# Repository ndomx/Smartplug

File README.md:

# Smartplug
WiFi controller for home automation

## Description
A smartplug is a device with which you can control the conection of an appliance remotely. As of version 2, I'm using an ESP8266 micro-controller, and controlling it using MQTT.

The schematics are publicly available in this repository, and the fabrication files are available in the releases page. All the required codes are also publicly available here, though you'll have to setup your Arduino IDE to program the MCU. Refer to the [libraries guide](./LIBRARIES_GUIDE.md) to learn how to do it.

## Functionality
### Basics
The basic operation of the smartplug is fairly simple. It's a commutator circuit just like those lights, found commonly in stairs, that can be controlled by two switches. The circuit goes as follows:

Current can flow through the load (a light bulb) when bith switches are in the same state. The smartplug works the same way, but instead of having two switches, it has two relays that are controlled by the MCU.

The MCU controls both signals, **RELAY_A** and **RELAY_B** that toggle each switch. One control signal is controlled remotely (via MQTT) while the other is controlled by an external switch.

The smartplug has two modes of operation:
1. Take absolute control of the load remotely, i.e. connect/disconnect the load remotely regardless of the external switch input
2. Use the smartplug as a traditional commutator circuit, i.e. the load will toggle every time each control signal is toggled, wether its via MQTT or physical input

> I noticed only one relay is necessary to achieve the same behaviour. So V3 will drop one relay and handle all the logic by software.

The mode of operation is controlled by the header J4.

### Power
The PCB traces were calculated for 5A max. In countries with 220V/50Hz supply, this can power 1kW loads. In countries with 110V/60Hz, the max output power is limited to 0.5kW.

On the other hand, all the electronics can be powered by the AC/DC module **X1**, or by external 5V connected to the USB connector, as shown in the image below.

Connect the jumper **J5** to enable power input from the AC/DC module, or leave disconnected and power via USB cable.
> Powering the device via USB cable is meant for uploading the firmware to the MCU. For other purposes, the use of the AC/DC module is recommended

### Current sensing
The smartplug is equipped with an ACS712 current sensor. The current is measured by the MCU ADC and uploaded to the server.

Additionally, if and overcurrent is detected, the OC flag will be activated (~OC as it is active low) and the output will be disabled.

The SN74LV (**U1**) is a quad NAND gate that implements the logic circuit that ensures the load remains unconnected while the OC flag is active.

When ~OC goes low, the outputs **RELAY_A** and **RELAY_B** will go HIGH/LOW repectively, thus, shutting down the load.

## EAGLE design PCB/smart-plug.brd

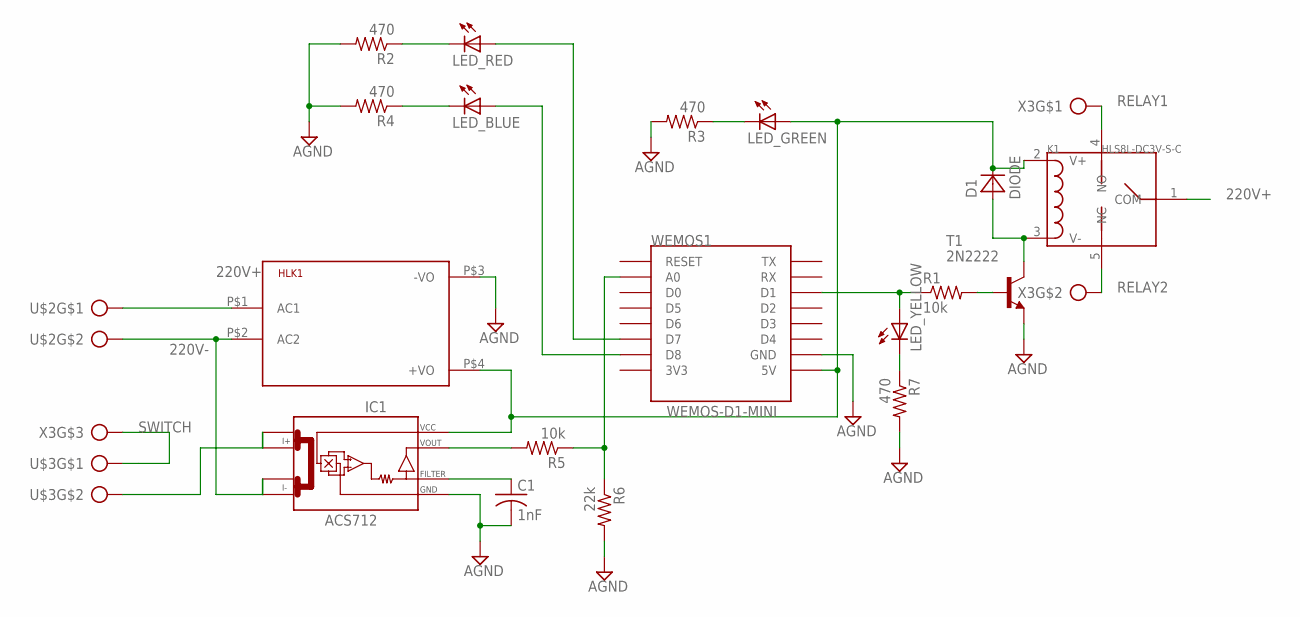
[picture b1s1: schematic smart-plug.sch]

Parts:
C1: 1nF; C1206
D1: DIODE; DO41-10
HLK1: HLK-SUPPLY; HLK-PM01
IC1: ACS712; SO08
K1: HLS8L-DC3V-S-C; REY5-19.0X15.0X15.0MM
LED_BLUE: LEDCHIP-LED0805; CHIP-LED0805
LED_GREEN: LEDCHIP-LED0805; CHIP-LED0805
LED_RED: LEDCHIP-LED0805; CHIP-LED0805
LED_YELLOW: LEDCHIP-LED0805; CHIP-LED0805
R1, R5: 10k; R1206
R2, R3, R4, R7: 470; R1206
R6: 22k; R1206
T1: 2N2222; TO92-EBC-OVAL
U$2, U$3: OUT-2PINS; AK300/2
WEMOS1: WEMOS-D1-MINI
X3: OUT-3PINS; AK300/3

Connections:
220V+: HLK1.P$1 (AC1), K1.1 (COM), U$2.1
220V-: HLK1.P$2 (AC2), IC1.4 (I-_1), U$2.2
AGND: C1.2, HLK1.P$3 (-VO), IC1.5 (GND), R2.2, R3.2, R4.2, R6.2, R7.2, T1.E, WEMOS1.GND
LED_BLUE: LED_BLUE.A, WEMOS1.D8
LED_GREEN: LED_GREEN.C, R3.1
LED_GREEN1: LED_YELLOW.C, R7.1
LED_RED: LED_RED.A, WEMOS1.D7
unnamed: IC1.2 (I+_1), U$3.2
unnamed: LED_YELLOW.A, R1.1, WEMOS1.D1
unnamed: R1.2, T1.B
unnamed: D1.C, HLK1.P$4 (+VO), IC1.8 (VCC), K1.2 (V+), LED_GREEN.A, WEMOS1.5V
unnamed: C1.1, IC1.6 (FILTER)
unnamed: D1.A, K1.3 (V-), T1.C
unnamed: IC1.7 (VOUT), R5.2
unnamed: R5.1, R6.1, WEMOS1.A0
unnamed: LED_RED.C, R2.1
unnamed: LED_BLUE.C, R4.1
RELAY1: K1.4 (NO), X3.1
RELAY2: K1.5 (NC), X3.2
SWITCH: U$3.1, X3.3

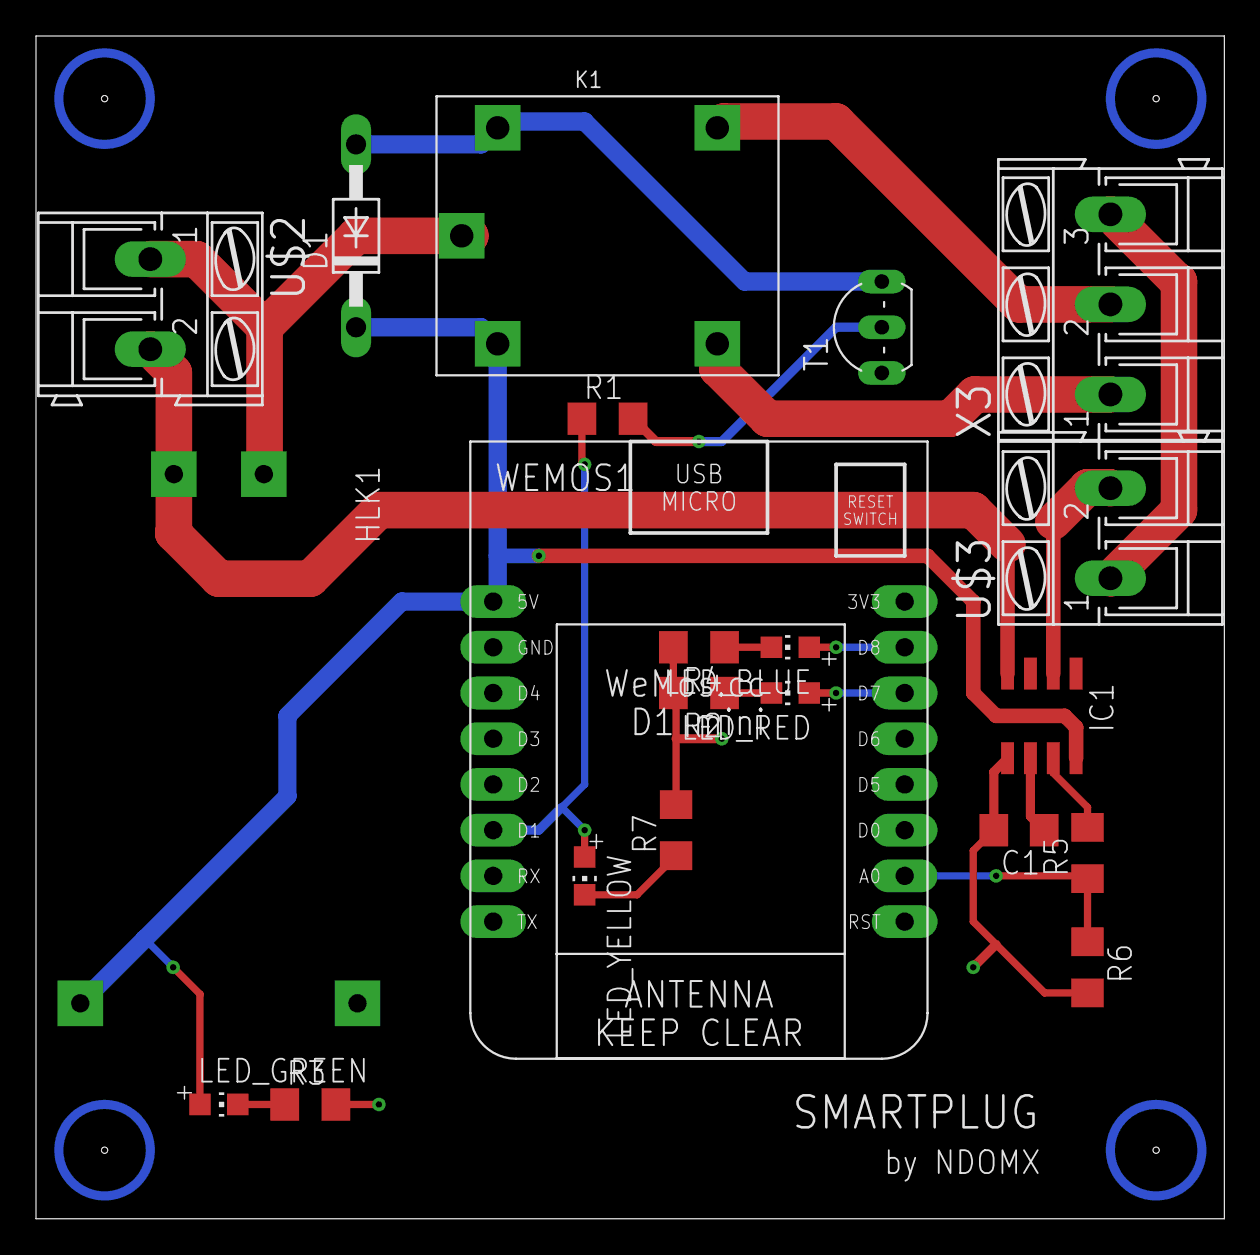
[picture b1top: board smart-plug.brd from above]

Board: 2 copper layers, 66.0 x 65.7 mm, 21 parts (0 on the bottom side), 20 nets.

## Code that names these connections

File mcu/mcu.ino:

#include <ESP8266WiFi.h>
#include <PubSubClient.h>

#include "private-data.h"

#define RELAY_PIN D1
#define LED_RED D6
#define LED_GREEN D7
#define LED_BLUE D8

String clientId = "ESP8266-light1"; // Be sure to change it for each device

WiFiClient espClient;
PubSubClient client(espClient);

bool blue_state = LOW;

void setup_wifi()
{
    delay(10);
    
    Serial.println();
    Serial.print("Connecting to ");
    Serial.println(ssid);

    WiFi.begin(ssid, password);

    while (WiFi.status() != WL_CONNECTED)
    {
        delay(500);
        Serial.print(".");

        digitalWrite(LED_BLUE, blue_state);
        blue_state ^= HIGH;
    }

    blue_state = LOW;
    digitalWrite(LED_BLUE, LOW);

    randomSeed(micros());

    Serial.println("");
    Serial.println("WiFi connected");
    Serial.println("IP address: ");
    Serial.println(WiFi.localIP());
}

void on_message(char *topic, byte *payload, unsigned int length)
{
    Serial.print(topic);
    Serial.print(" | ");
    for (int i = 0; i < length; i++)
    {
        Serial.print((char)payload[i]);
    }
    Serial.println();
    
    digitalWrite(RELAY_PIN, payload[0] == '1');

    blink_led();
}

void reconnect()
{
    digitalWrite(LED_RED, HIGH);
    digitalWrite(LED_GREEN, HIGH);
    while (!client.connected())
    {
        Serial.print("Attempting MQTT connection...");
        
        if (client.connect(clientId.c_str()))
        {
            Serial.println("connected");
            client.subscribe(topic);
        }
        else
        {
            Serial.print("failed, rc=");
            Serial.print(client.state());
            Serial.println(" try again in 5 seconds");
            delay(5000);
        }

        blue_state ^= HIGH;
        digitalWrite(LED_BLUE, blue_state);
    }
    digitalWrite(LED_RED, LOW);
    digitalWrite(LED_GREEN, HIGH);
    digitalWrite(LED_BLUE, LOW);
}

void blink_led()
{
    digitalWrite(LED_BLUE, LOW);
    delay(300);
    digitalWrite(LED_BLUE, HIGH);
    delay(300);
    digitalWrite(LED_BLUE, LOW);
    delay(300);
    digitalWrite(LED_BLUE, HIGH);
}

void setup()
{
    pinMode(RELAY_PIN, OUTPUT);

    Serial.begin(115200);
    setup_wifi();
    client.setServer(mqtt_server, 1883);
    client.setCallback(on_message);

    digitalWrite(RELAY_PIN, LOW);

    client.subscribe(topic);
}

void loop()
{
    if (!client.connected())
    {
        reconnect();
    }
    client.loop();
}

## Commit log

2018-10-07 Update file
    Updated .gitignore to ommit Eagle PCB and editor autogenerated files
2018-10-07 Update file
    Removed private data from repository
2018-10-07 Add files
    ESP8266 source code and an example of the required data in header file
2018-10-07 Add files
    Eagle PCB design for Smartplug
2018-10-07 Add files
    Nodejs REST API to communicate with end devices
2018-10-07 Update files
    Added LED indicators
2018-12-20 Update mcu_mqtt/dummy-private-data.h
    Add file description
2018-12-20 Delete files
    Deleted old files
2018-12-20 Delete files
    Deleted files
2018-12-20 Update files
    Improved led debugging
2018-12-20 Update files
    Added on board LEDs, updated design
2018-12-20 Update mcu_mqtt.ino
    Changed RED LED pin
2018-12-20 Update .gitignore
    Removed old files
2018-12-21 Update mcu_mqtt.ino
    Set LED pins to output
2018-12-21 Create smartplug-components.lbr
    Added smartplug-components library for Eagle
2018-12-21 Update dummy-private-data.h
    Improved file description
2018-12-21 Update mcu_mqtt.ino
    Added file description
2018-12-21 Update smartplug-functions.h
    Added description
2018-12-21 Update README.md
    Completed README
2019-01-12 Update files
    Removed fuse and made PCB smaller
2019-01-12 Add files via upload
    Gerber files for PCB fabrication
2019-01-13 Renamed files
2019-01-13 Update mcu_mqtt.ino
    Added current sensor and now the smartplug supports not only to toggle on/off but to choose the state
2019-01-14 Update PCB files
    Improved design, added SMD components and current sensor
2020-11-06 PCB Version 2
    Newly improved design in Altium
2020-11-07 Folder Restructuration
2020-11-07 Update docs
2020-11-07 Add altium files to repository
2020-11-07 Fix wiring mistake
2020-11-07 Update firmware to v2
2020-11-10 Update to V3
2020-11-10 Make schematics update
2020-11-16 Update schematics
2021-04-06 Finish v3 design
